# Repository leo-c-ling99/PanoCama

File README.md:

# PanoCama
Have you ever want to take a panoramic photo, automatically? The PanoCama is a low-cost device for taking wide-angle photographs. With its dual-cameras, it's able to roughly measure depth for fast environmental mapping.

This camera system was made with the mini-pan tilt system from Adafruit, an ESP32 DEVKIT, and two ArduCAM 2MP cameras. Image stitching and stereo vision components are performed using the OpenCV library for Python.

Project for EE 327: Electronic System Design II.

## Organization
The code I developed over the course is ordered here into Firmware, Image Processing, and Web sections. This project is organized as multiple proof of concepts for the various sections rather than one project with all components nicely interfaced together. Firmware is primarily C/C++ code developed for an ESP32 DEVKIT V1 for the Arduino Environment developed using PlatformIO. Image Processing is primarily Python code exploring the OpenCV library. Web is mostly setup code for an Tornado server with WebSockets and a webpage interface. PCB contains the two boards designed for this project. 

As of now, to interface the ESP32 with the Tornado Webserver, the address of the server and the local WiFi password must be changed within the main.cpp file.

3D mount: https://cad.onshape.com/documents/40f7b32b21ebe9fb9dda074d/w/69e21c5f167fa995fddc0409/e/9e02c831b684e933273a17e4

### Copyright © 2021 Leo Ling

Permission is hereby granted, free of charge, to any person obtaining a copy of this software and associated documentation files (the “Software”), to deal in the Software without restriction, including without limitation the rights to use, copy, modify, merge, publish, distribute, sublicense, and/or sell copies of the Software, and to permit persons to whom the Software is furnished to do so, subject to the following conditions:

The above copyright notice and this permission notice shall be included in all copies or substantial portions of the Software.

THE SOFTWARE IS PROVIDED “AS IS”, WITHOUT WARRANTY OF ANY KIND, EXPRESS OR IMPLIED, INCLUDING BUT NOT LIMITED TO THE WARRANTIES OF MERCHANTABILITY, FITNESS FOR A PARTICULAR PURPOSE AND NONINFRINGEMENT. IN NO EVENT SHALL THE AUTHORS OR COPYRIGHT HOLDERS BE LIABLE FOR ANY CLAIM, DAMAGES OR OTHER LIABILITY, WHETHER IN AN ACTION OF CONTRACT, TORT OR OTHERWISE, ARISING FROM, OUT OF OR IN CONNECTION WITH THE SOFTWARE OR THE USE OR OTHER DEALINGS IN THE SOFTWARE.

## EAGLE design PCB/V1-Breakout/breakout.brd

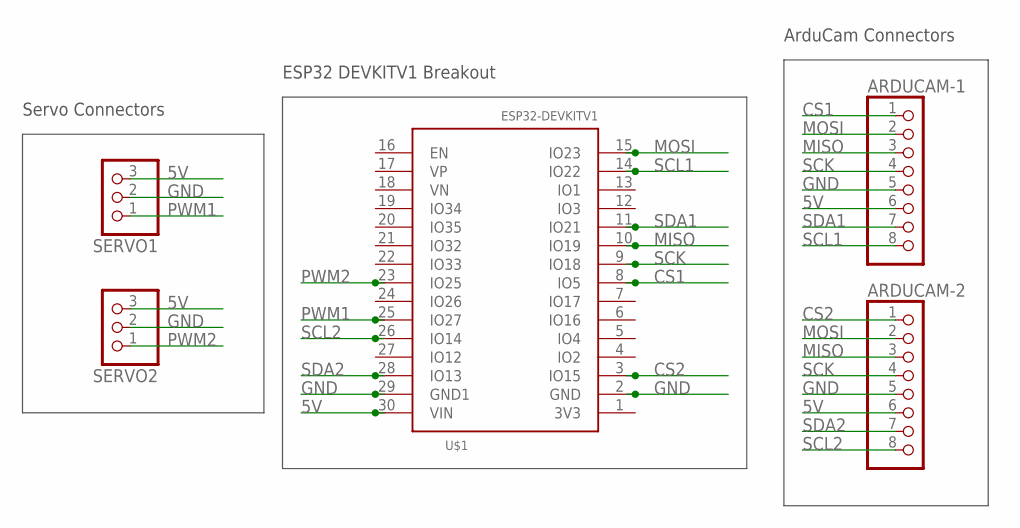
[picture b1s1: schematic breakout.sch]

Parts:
ARDUCAM-1, ARDUCAM-2: PINHD-1X8BIG; 1X08-BIG
SERVO1, SERVO2: PINHD-1X3; 1X03
U$1: ESP32DEVKITV1; ESP32-DEVKITV1

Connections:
5V: ARDUCAM-1.6, ARDUCAM-2.6, SERVO1.3, SERVO2.3, U$1.30 (VIN)
CS1: ARDUCAM-1.1, U$1.8 (IO5)
CS2: ARDUCAM-2.1, U$1.3 (IO15)
GND: ARDUCAM-1.5, ARDUCAM-2.5, SERVO1.2, SERVO2.2, U$1.2 (GND), U$1.29 (GND1)
MISO: ARDUCAM-1.3, ARDUCAM-2.3, U$1.10 (IO19)
MOSI: ARDUCAM-1.2, ARDUCAM-2.2, U$1.15 (IO23)
PWM1: SERVO1.1, U$1.25 (IO27)
PWM2: SERVO2.1, U$1.23 (IO25)
SCK: ARDUCAM-1.4, ARDUCAM-2.4, U$1.9 (IO18)
SCL1: ARDUCAM-1.8, U$1.14 (IO22)
SCL2: ARDUCAM-2.8, U$1.26 (IO14)
SDA1: ARDUCAM-1.7, U$1.11 (IO21)
SDA2: ARDUCAM-2.7, U$1.28 (IO13)

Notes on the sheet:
Servo Connectors
ESP32 DEVKITV1 Breakout
ArduCam Connectors

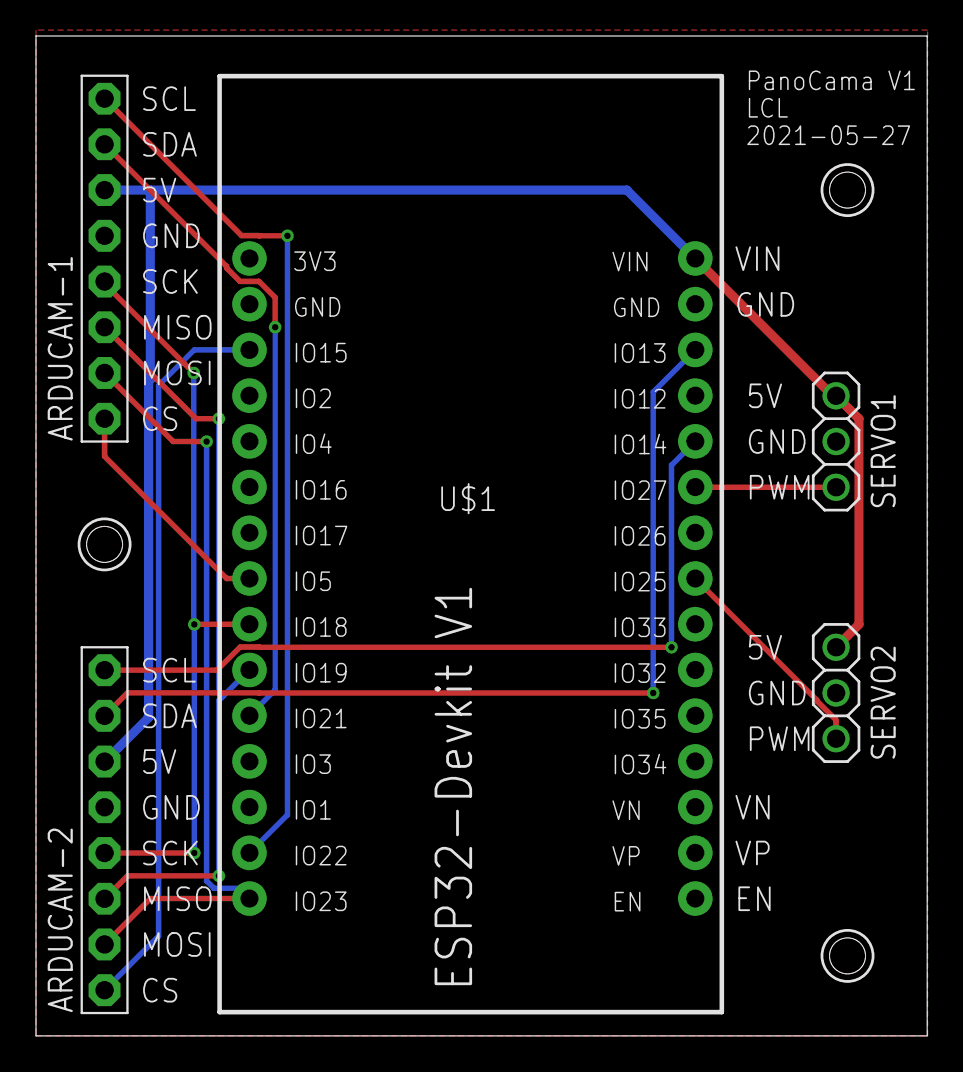
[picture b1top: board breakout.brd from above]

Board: 2 copper layers, 49.5 x 55.5 mm, 5 parts (0 on the bottom side), 13 nets.

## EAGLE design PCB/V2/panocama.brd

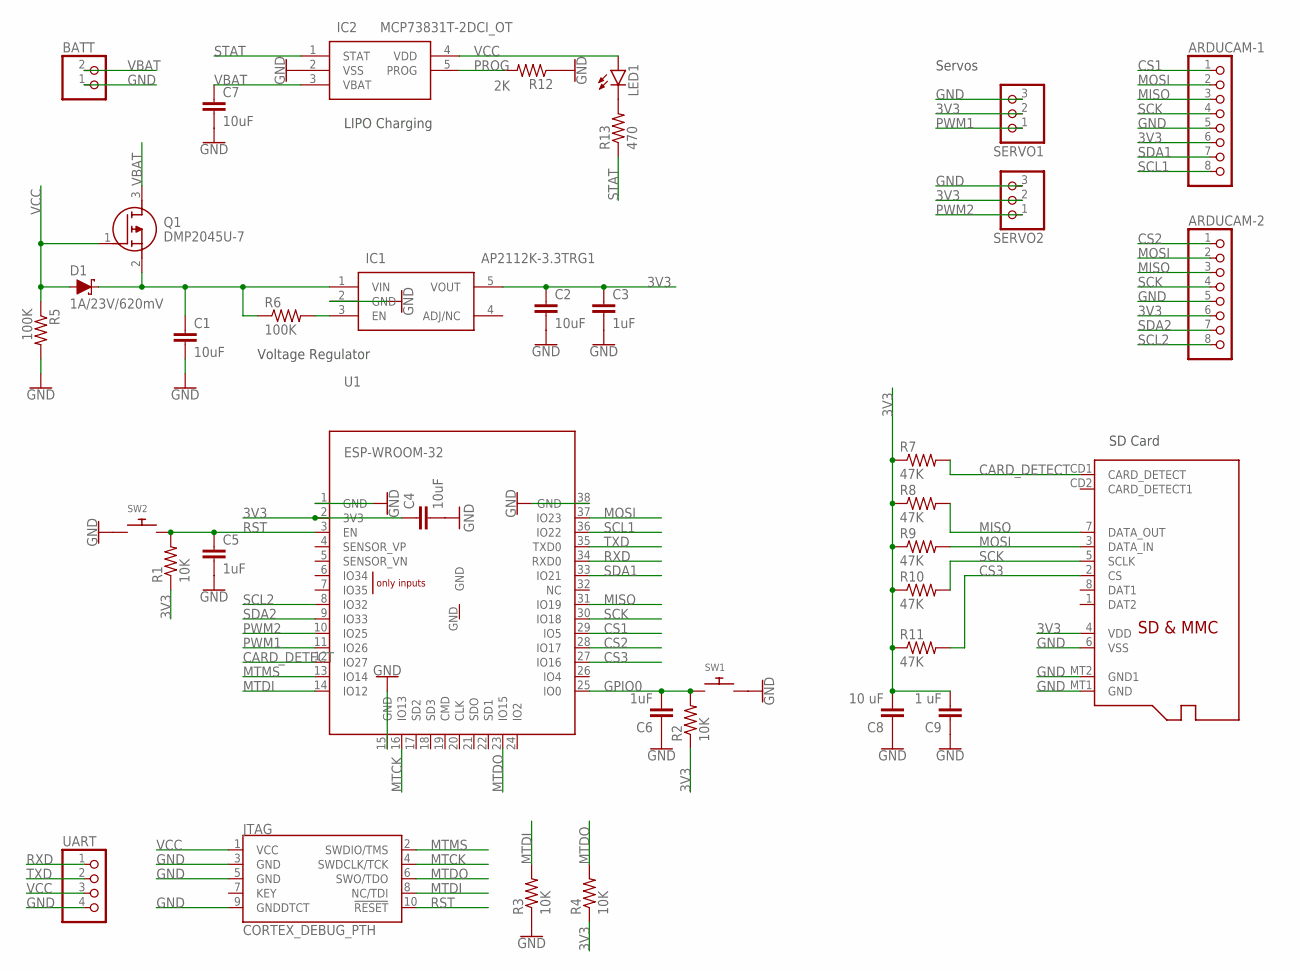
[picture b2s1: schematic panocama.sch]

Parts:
ARDUCAM-1, ARDUCAM-2: PINHD-1X8CLEANBIG; 1X08-CLEANBIG
BATT: JST_2PIN-SMT; JST-PH-2-SMT
C1, C2, C4, C7: 10uF; 0805
C3, C5, C6: 1uF; 0805
C8: 10 uF; 0805
C9: 1 uF; 0805
D1: 1A/23V/620mV; SOD-323
IC1: AP2112K-3.3TRG1; SOT95P282X130-5N
IC2: MCP73831T-2DCI_OT; SOT95P270X145-5N
JTAG: CORTEX_DEBUG_PTH; 2X5-PTH-1.27MM
LED1: LED0603; LED-0603
Q1: DMP2045U-7; SOT96P240X110-3N
R1, R2, R3, R4: 10K; 0805
R5, R6: 100K; 0805
R7, R8, R9, R10, R11: 47K; 0805
R12: 2K; 0805
R13: 470; 0805
SD: MICROSD
SERVO1, SERVO2: PINHD-1X3; 1X03
SW1, SW2: SWITCH_PUSHBUTTONSOFTTOUCHSMD_SJ; PUSHBUTTON_SMD_SJ
U1: ESP-WROOM-32
UART: PINHD-1X4; 1X04

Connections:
3V3: ARDUCAM-1.6, ARDUCAM-2.6, C2.1, C3.1, C4.1, C8.2, C9.2, IC1.5 (VOUT), R1.1, R2.1, R4.1, R7.1, R8.1, R9.1, R10.1, R11.1, SD.4 (VDD), SERVO1.2, SERVO2.2, U1.2 (3V3)
CARD_DETECT: R7.2, SD.CD1 (CARD_DETECT), U1.12 (IO27)
CS1: ARDUCAM-1.1, U1.29 (IO5)
CS2: ARDUCAM-2.1, U1.28 (IO17)
CS3: R11.2, SD.2 (CS), U1.27 (IO16)
GND: ARDUCAM-1.5, ARDUCAM-2.5, BATT.1 (2), C1.2, C2.2, C3.2, C4.2, C5.2, C6.1, C7.2, C8.1, C9.1, IC1.2 (GND), IC2.2 (VSS), JTAG.3 (GND), JTAG.5 (GND), JTAG.9 (GNDDTCT), R3.1, R5.2, R12.1, SD.6 (VSS), SD.MT1 (GND), SD.MT2 (GND1), SERVO1.3, SERVO2.3, SW1.P$2, SW2.P$1, U1.1 (GND), U1.15 (GND), U1.38 (GND), UART.4
GPIO0: C6.2, R2.2, SW1.P$1, U1.25 (IO0)
MISO: ARDUCAM-1.3, ARDUCAM-2.3, R8.2, SD.7 (DATA_OUT), U1.31 (IO19)
MOSI: ARDUCAM-1.2, ARDUCAM-2.2, R9.2, SD.3 (DATA_IN), U1.37 (IO23)
MTCK: JTAG.4 (SWDCLK/TCK), U1.16 (IO13)
MTDI: JTAG.8 (NC/TDI), R3.2, U1.14 (IO12)
MTDO: JTAG.6 (SWO/TDO), R4.2, U1.23 (IO15)
MTMS: JTAG.2 (SWDIO/TMS), U1.13 (IO14)
unnamed: IC1.3 (EN), R6.2
unnamed: C1.1, D1.C, IC1.1 (VIN), Q1.2 (S), R6.1
unnamed: LED1.C, R13.2
PROG: IC2.5 (PROG), R12.2
PWM1: SERVO1.1, U1.11 (IO26)
PWM2: SERVO2.1, U1.10 (IO25)
RST: C5.1, JTAG.10 (!RESET), R1.2, SW2.P$2, U1.3 (EN)
RXD: U1.34 (RXD0), UART.1
SCK: ARDUCAM-1.4, ARDUCAM-2.4, R10.2, SD.5 (SCLK), U1.30 (IO18)
SCL1: ARDUCAM-1.8, U1.36 (IO22)
SCL2: ARDUCAM-2.8, U1.8 (IO32)
SDA1: ARDUCAM-1.7, U1.33 (IO21)
SDA2: ARDUCAM-2.7, U1.9 (IO33)
STAT: IC2.1 (STAT), R13.1
TXD: U1.35 (TXD0), UART.2
VBAT: BATT.2 (1), C7.1, IC2.3 (VBAT), Q1.3 (D)
VCC: D1.A, IC2.4 (VDD), JTAG.1 (VCC), LED1.A, Q1.1 (G), R5.1, UART.3

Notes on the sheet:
LIPO Charging
Voltage Regulator
SD Card
Servos

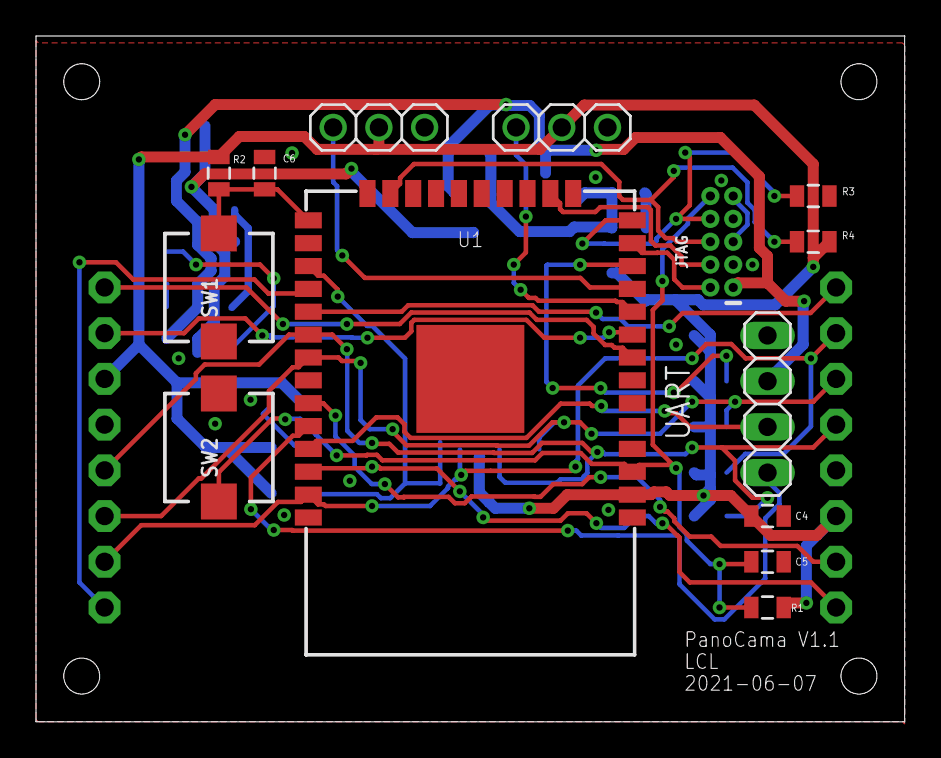
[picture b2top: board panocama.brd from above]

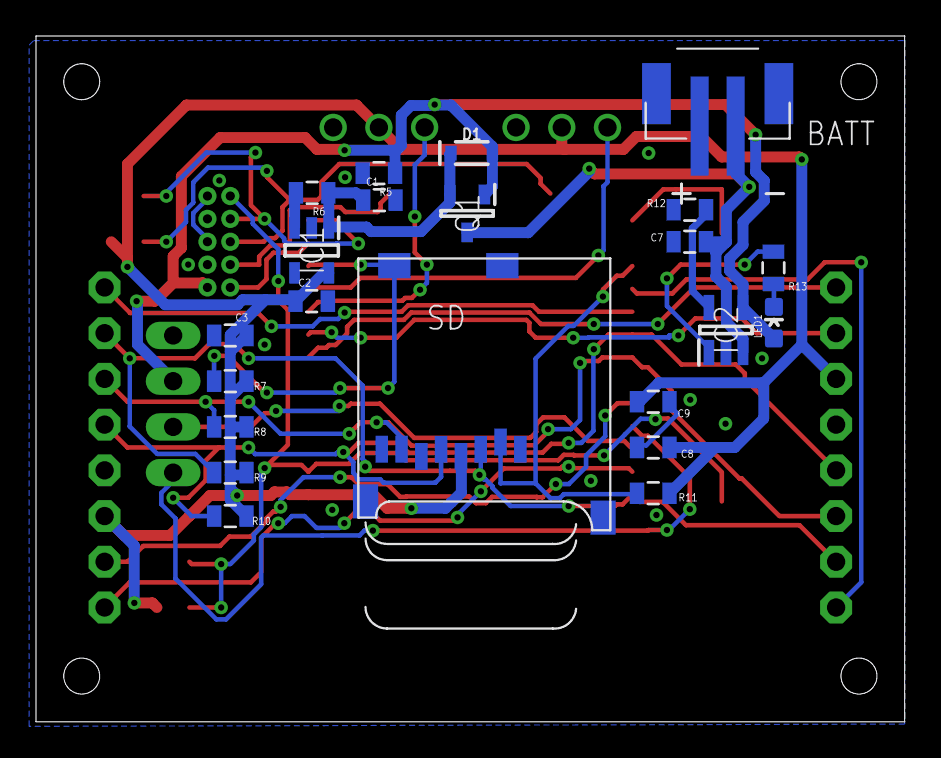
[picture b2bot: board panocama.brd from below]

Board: 2 copper layers, 48.3 x 38.1 mm, 38 parts (22 on the bottom side), 30 nets.

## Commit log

2021-06-10 Initial Commit with all folders
2021-06-10 Added PCBs

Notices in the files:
parts and their libraries:
SparkFun-DiscreteSemi: Licensing: Creative Commons ShareAlike 4.0 International - https://creativecommons.org/licenses/by-sa/4.0
